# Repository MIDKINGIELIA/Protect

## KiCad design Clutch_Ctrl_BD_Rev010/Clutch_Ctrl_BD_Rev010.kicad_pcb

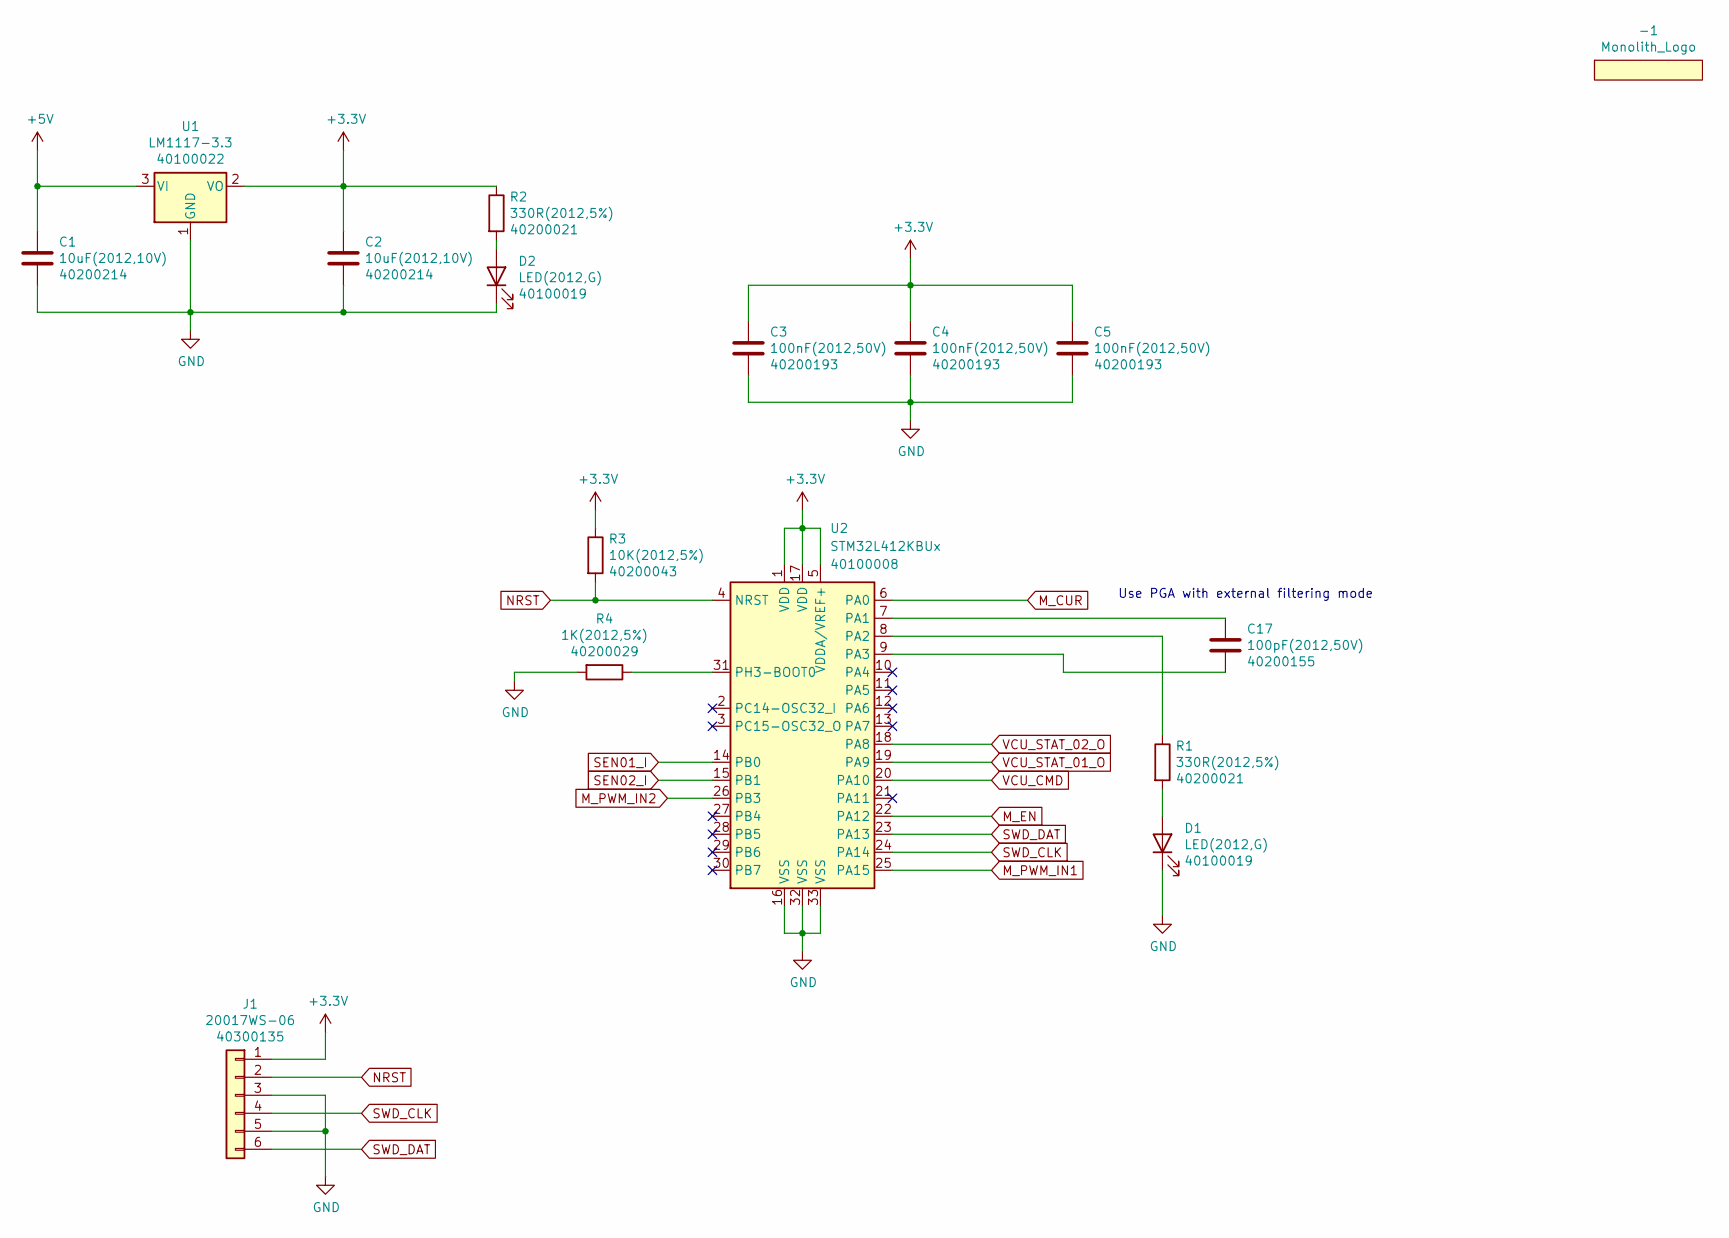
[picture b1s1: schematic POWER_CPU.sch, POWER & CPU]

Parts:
-1: Monolith_Logo
C1, C2: 10uF(2012,10V); C_0805_2012Metric; PartNo 40200214
C3, C4, C5: 100nF(2012,50V); C_0805_2012Metric; PartNo 40200193
C17: 100pF(2012,50V); C_0805_2012Metric; PartNo 40200155
D1, D2: LED(2012,G); LED_0805_2012Metric; PartNo 40100019
J1: 20017WS-06; Yeonho_20017WS-06_P2.0mm; PartNo 40300135
R1, R2: 330R(2012,5%); R_0805_2012Metric; PartNo 40200021
R3: 10K(2012,5%); R_0805_2012Metric; PartNo 40200043
R4: 1K(2012,5%); R_0805_2012Metric; PartNo 40200029
U1: LM1117-3.3; SOT-223-3_TabPin2; PartNo 40100022
U2: STM32L412KBUx; QFN-32-1EP_5x5mm_P0.5mm_EP3.45x3.45mm; PartNo 40100008

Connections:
+3V3: C2.1, C3.1, C4.1, C5.1, J1.1, R2.1, R3.1, U1.2 (VO), U2.1 (VDD), U2.5 (VDDA/VREF+), U2.17 (VDD); also elsewhere on the board
+5V: C1.1, U1.3 (VI); also elsewhere on the board
GND: C1.2, C2.2, C3.2, C4.2, C5.2, D1.1 (K), D2.1 (K), J1.3, J1.5, R4.2, U1.1 (GND), U2.16 (VSS), U2.32 (VSS), U2.33 (VSS); also elsewhere on the board
M_CUR: U2.6 (PA0); also elsewhere on the board
M_EN: U2.22 (PA12); also elsewhere on the board
M_PWM_IN1: U2.25 (PA15); also elsewhere on the board
M_PWM_IN2: U2.26 (PB3); also elsewhere on the board
NRST: J1.2, R3.2, U2.4 (NRST)
unnamed: C17.1, U2.7 (PA1)
unnamed: C17.2, U2.9 (PA3)
unnamed: D1.2 (A), R1.2
unnamed: D2.2 (A), R2.2
unnamed: R1.1, U2.8 (PA2)
unnamed: R4.1, U2.31 (PH3-BOOT0)
SEN01_I: U2.14 (PB0); also elsewhere on the board
SEN02_I: U2.15 (PB1); also elsewhere on the board
SWD_CLK: J1.4, U2.24 (PA14)
SWD_DAT: J1.6, U2.23 (PA13)
VCU_CMD: U2.20 (PA10); also elsewhere on the board
VCU_STAT_01_O: U2.19 (PA9); also elsewhere on the board
VCU_STAT_02_O: U2.18 (PA8); also elsewhere on the board

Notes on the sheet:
Use PGA with external filtering mode

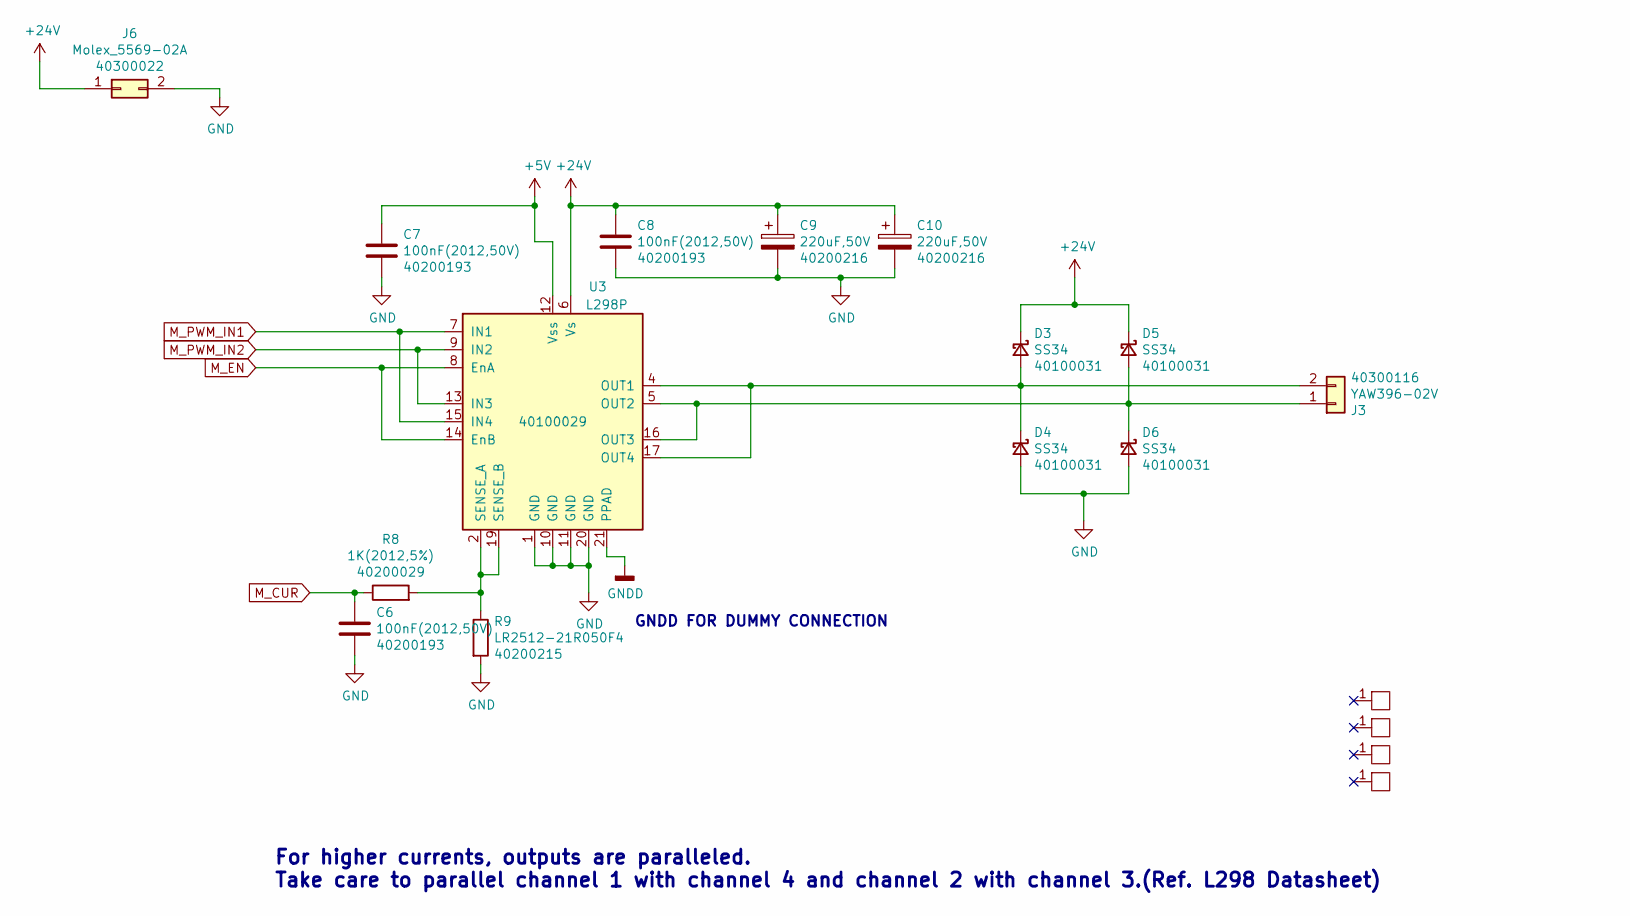
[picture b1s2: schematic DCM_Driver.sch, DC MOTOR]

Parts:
C6, C7, C8: 100nF(2012,50V); C_0805_2012Metric; PartNo 40200193
C9, C10: 220uF,50V; CP_Radial_D10.0mm_P5.00mm; PartNo 40200216
D3, D4, D5, D6: SS34; D_SMB; PartNo 40100031
H1, H2, H3, H4: PTH-HOLE-M3-CIRCLE; PTH-CIRCLE-M3
J3: YAW396-02V; PartNo 40300116
J6: Molex_5569-02A; Molex_Mini-Fit_Jr_5569-02A1_2x01_P4.20mm_Horizontal; PartNo 40300022
R8: 1K(2012,5%); R_0805_2012Metric; PartNo 40200029
R9: LR2512-21R050F4; R_2512_6332Metric; PartNo 40200215
U3: L298P; HSOP-20-1EP_11.0x15.9mm_P1.27mm_SlugDown; PartNo 40100029

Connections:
+5V: C7.1, U3.12 (Vss); also elsewhere on the board
+24V: C8.1, C9.1, C10.1, D3.1 (K), D5.1 (K), J6.1, U3.6 (Vs)
GND: C6.2, C7.2, C8.2, C9.2, C10.2, D4.2 (A), D6.2 (A), J6.2, R9.2, U3.1 (GND), U3.10 (GND), U3.11 (GND), U3.20 (GND); also elsewhere on the board
GNDD: U3.21 (PPAD)
M_CUR: C6.1, R8.1; also elsewhere on the board
M_EN: U3.8 (EnA), U3.14 (EnB); also elsewhere on the board
M_PWM_IN1: U3.7 (IN1), U3.15 (IN4); also elsewhere on the board
M_PWM_IN2: U3.9 (IN2), U3.13 (IN3); also elsewhere on the board
unnamed: D3.2 (A), D4.1 (K), J3.2, U3.4 (OUT1), U3.17 (OUT4)
unnamed: D5.2 (A), D6.1 (K), J3.1, U3.5 (OUT2), U3.16 (OUT3)
unnamed: R8.2, R9.1, U3.2 (SENSE_A), U3.19 (SENSE_B)

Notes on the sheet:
For higher currents, outputs are paralleled. Take care to parallel channel 1 with channel 4 and channel 2 with channel 3.(Ref. L298 Datasheet)
GNDD FOR DUMMY CONNECTION

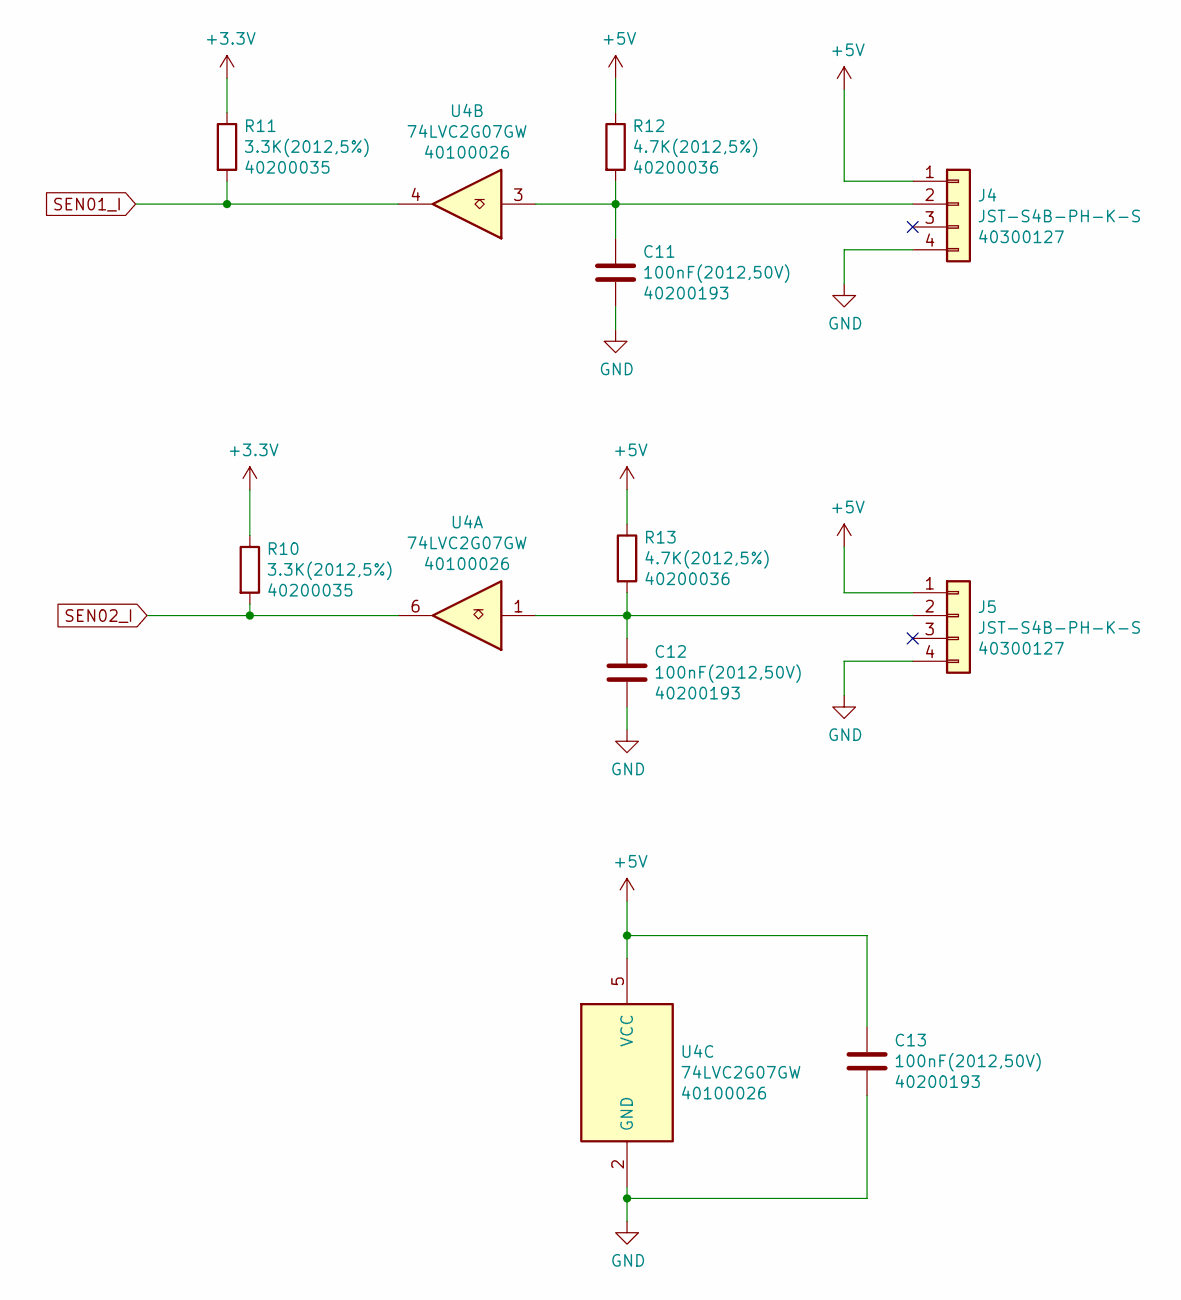
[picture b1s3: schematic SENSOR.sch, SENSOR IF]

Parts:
C11, C12, C13: 100nF(2012,50V); C_0805_2012Metric; PartNo 40200193
J4, J5: JST-S4B-PH-K-S; JST_PH_S4B-PH-K_1x04_P2.00mm_Horizontal; PartNo 40300127
R10, R11: 3.3K(2012,5%); R_0805_2012Metric; PartNo 40200035
R12, R13: 4.7K(2012,5%); R_0805_2012Metric; PartNo 40200036
U4: 74LVC2G07GW; SOT-363_SC-70-6; PartNo 40100026

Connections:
+3V3: R10.1, R11.1; also elsewhere on the board
+5V: C13.1, J4.1, J5.1, R12.1, R13.1, U4.5 (VCC); also elsewhere on the board
GND: C11.2, C12.2, C13.2, J4.4, J5.4, U4.2 (GND); also elsewhere on the board
unnamed: C11.1, J4.2, R12.2, U4.3
unnamed: C12.1, J5.2, R13.2, U4.1
SEN01_I: R11.2, U4.4; also elsewhere on the board
SEN02_I: R10.2, U4.6; also elsewhere on the board

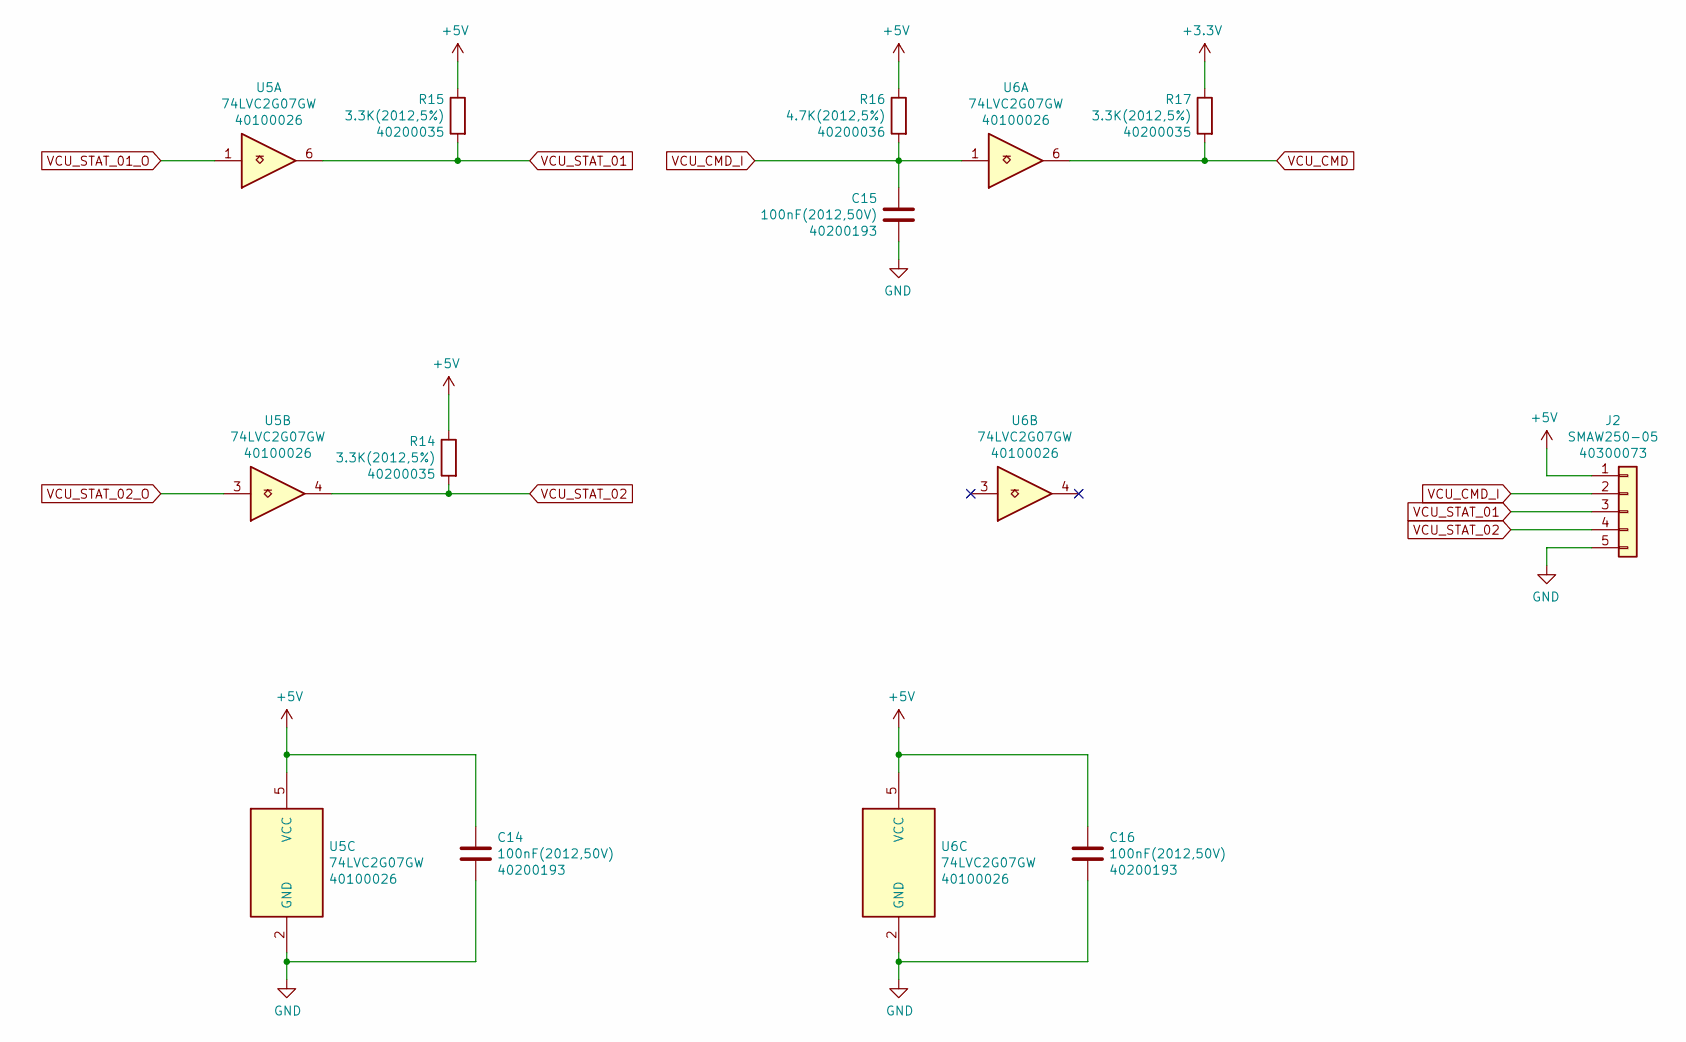
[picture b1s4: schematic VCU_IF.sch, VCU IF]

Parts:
C14, C15, C16: 100nF(2012,50V); C_0805_2012Metric; PartNo 40200193
J2: SMAW250-05; PartNo 40300073
R14, R15, R17: 3.3K(2012,5%); R_0805_2012Metric; PartNo 40200035
R16: 4.7K(2012,5%); R_0805_2012Metric; PartNo 40200036
U5, U6: 74LVC2G07GW; SOT-363_SC-70-6; PartNo 40100026

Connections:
+3V3: R17.1; also elsewhere on the board
+5V: C14.1, C16.1, J2.1, R14.1, R15.1, R16.1, U5.5 (VCC), U6.5 (VCC); also elsewhere on the board
GND: C14.2, C15.2, C16.2, J2.5, U5.2 (GND), U6.2 (GND); also elsewhere on the board
VCU_CMD: R17.2, U6.6; also elsewhere on the board
VCU_CMD_I: C15.1, J2.2, R16.2, U6.1
VCU_STAT_01: J2.3, R15.2, U5.6
VCU_STAT_01_O: U5.1; also elsewhere on the board
VCU_STAT_02: J2.4, R14.2, U5.4
VCU_STAT_02_O: U5.3; also elsewhere on the board

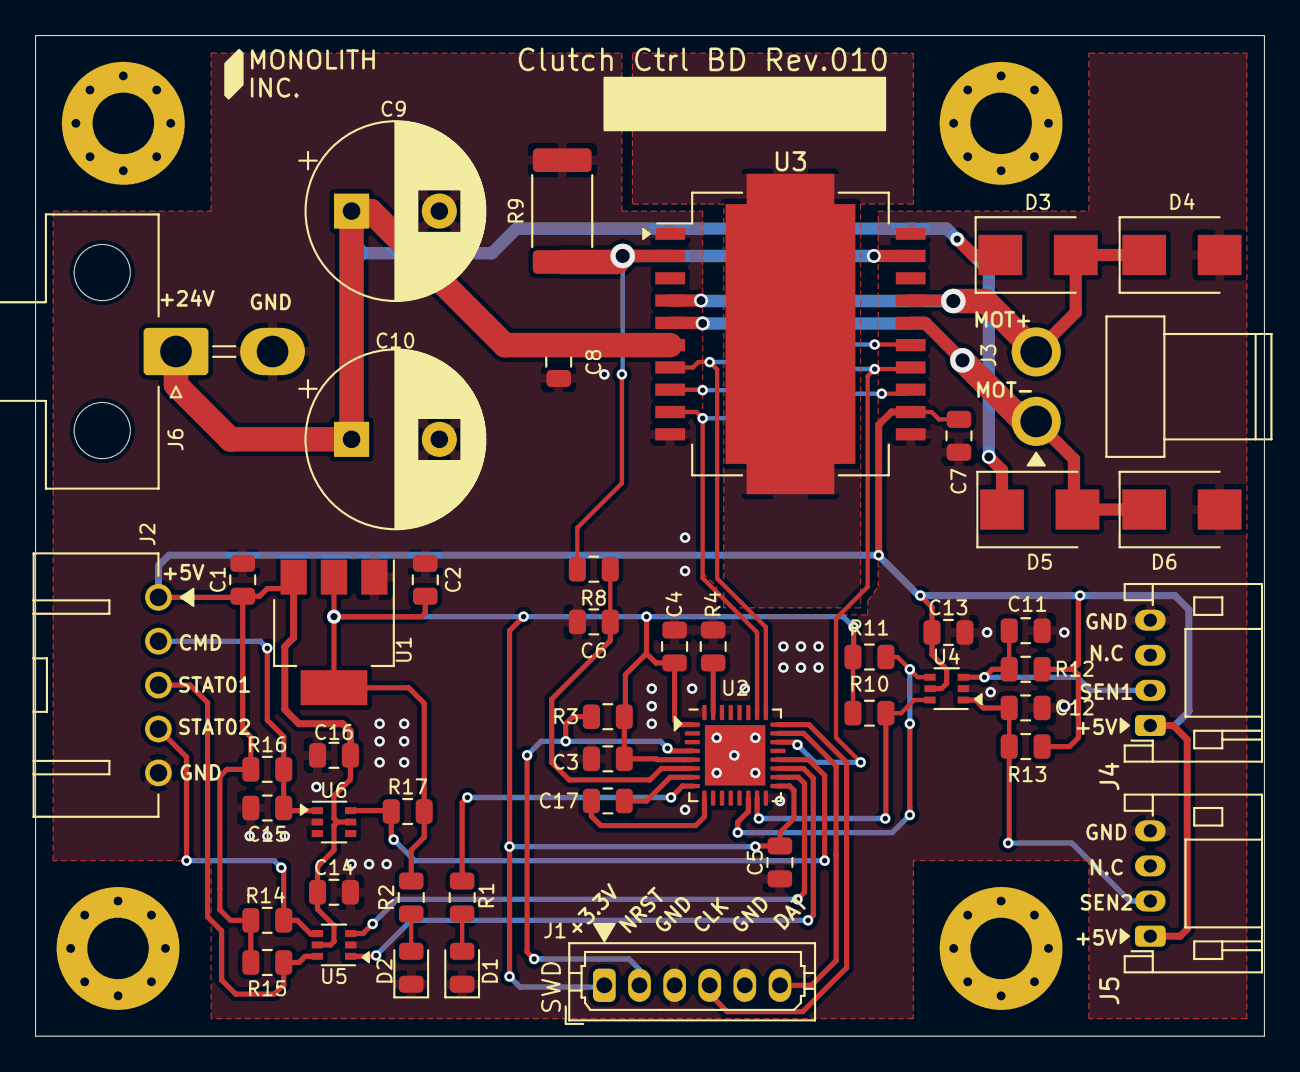
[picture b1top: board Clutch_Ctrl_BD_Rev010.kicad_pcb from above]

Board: 2 copper layers, 70.0 x 57.0 mm, 54 parts (0 on the bottom side), 30 nets.

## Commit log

2022-12-25 Add files via upload
    12/25
